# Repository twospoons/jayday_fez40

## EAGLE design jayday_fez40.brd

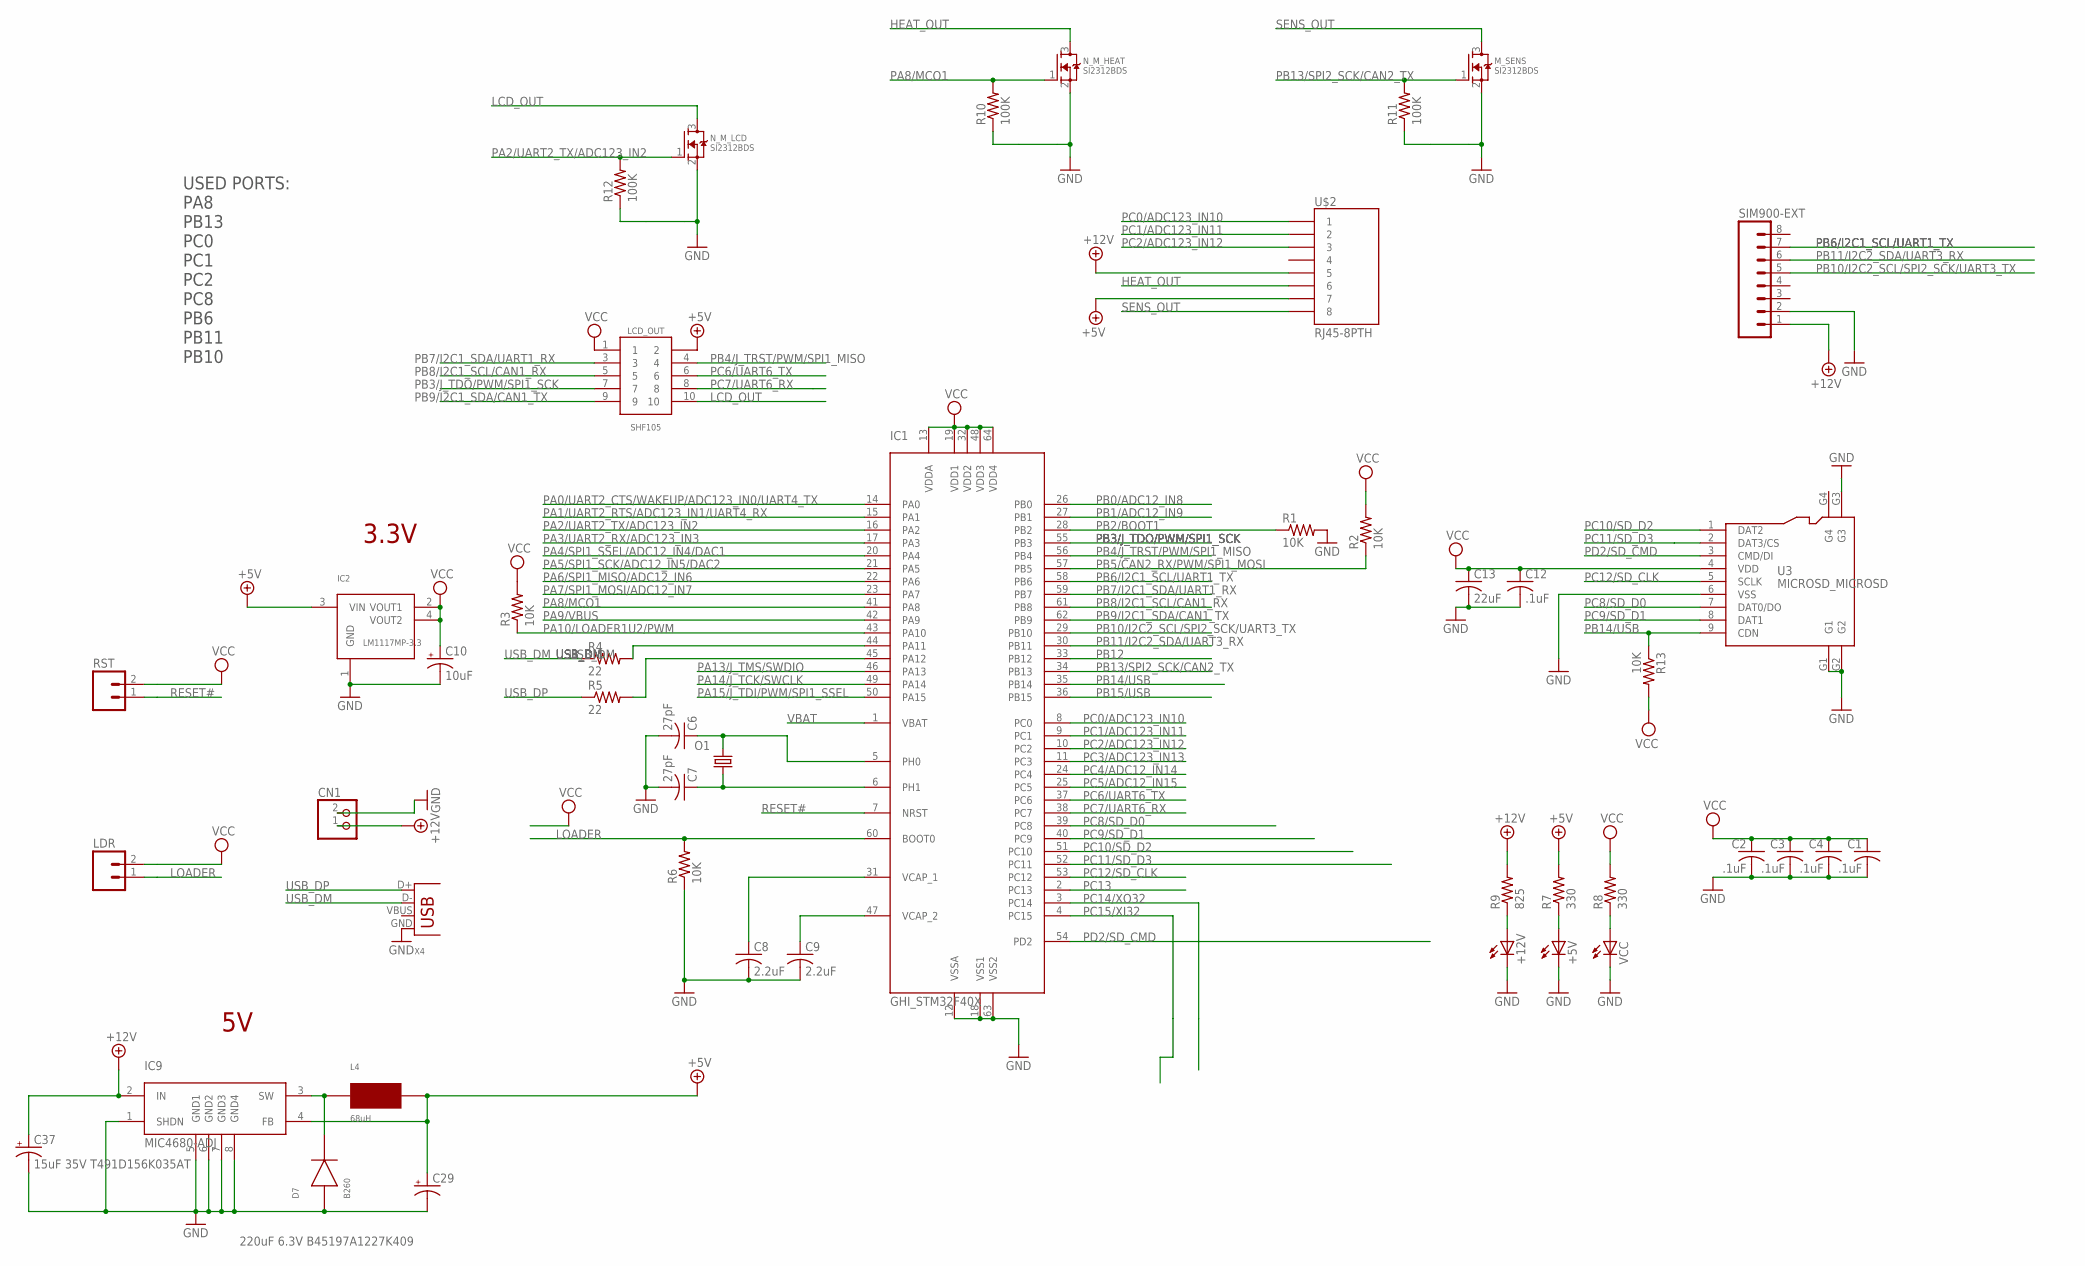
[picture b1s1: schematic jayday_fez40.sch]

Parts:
+5V, +12V: LEDCHIPLED_0805; CHIPLED_0805
C1, C2, C3, C4, C12: .1uF; C0603K
C6, C7: 27pF; C0603K
C8, C9: 2.2uF; C0805K
C10: 10uF; CT3528
C13: 22uF; C0805K
C29: 220uF 6.3V B45197A1227K409; D/7343-31W
C37: 15uF 35V T491D156K035AT; D/7343-31W
CN1: JST_2PIN-THM-RA; JST-PH-2-THM-RA
D7: B260; DIODE_SMA
IC1: GHI_STM32F40X; GHI_LQFP64
IC2: LM1117MP-3.3; SOT223
IC9: MIC4680-ADJ; SO8
L4: 68uH; UP2BXXX
LCD_OUT: SHF105; GAD_PAC_SMD
LDR: M02PTH; 1X02
M_SENS: SI2312BDS; TO-236
N_M_HEAT: SI2312BDS; TO-236
N_M_LCD: SI2312BDS; TO-236
O1: 12Mhz; SM49@1
R1, R2, R3, R6, R13: 10K; R0603
R4, R5: 22; R0603
R7, R8: 330; R0603
R9: 825; R0603
R10, R11, R12: 100K; R0603
RST: M02PTH; 1X02
SIM900-EXT: M081X08; 1X08
U3: MICROSD_MICROSD
U$2: RJ45-8PTH; RJ45-8
VCC: LEDCHIPLED_0805; CHIPLED_0805
X4: DX2R005HN2E700; USB-MB-S

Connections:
+5V: C29.+, IC2.3 (VIN), IC9.4 (FB), L4.P$2 (2), LCD_OUT.2, R7.2, U$2.7
+12V: C37.+, CN1.1 (2), IC9.2 (IN), R9.2, SIM900-EXT.1, U$2.5
GND: +5V.C, +12V.C, C1.2, C2.2, C3.2, C4.2, C6.2, C7.2, C8.2, C9.2, C10.-, C12.2, C13.2, C29.-, C37.-, CN1.2 (1), D7.A, IC1.12 (VSSA), IC1.18 (VSS1), IC1.63 (VSS2), IC2.1 (GND), IC9.1 (SHDN), IC9.5 (GND1), IC9.6 (GND2), IC9.7 (GND3), IC9.8 (GND4), M_SENS.2 (S), N_M_HEAT.2 (S), N_M_LCD.2 (S), R1.2, R6.1, R10.1, R11.1, R12.1, SIM900-EXT.2, U3.6 (VSS), U3.G1, U3.G2, U3.G3, VCC.C, X4.GND
HEAT_OUT: N_M_HEAT.3 (D), U$2.6
LCD_OUT: LCD_OUT.10, N_M_LCD.3 (D)
LOADER: IC1.60 (BOOT0), LDR.1, R6.2
unnamed: C9.1, IC1.47 (VCAP_2)
unnamed: C8.1, IC1.31 (VCAP_1)
unnamed: IC1.44 (PA11), R4.2
unnamed: IC1.45 (PA12), R5.2
unnamed: D7.K, IC9.3 (SW), L4.P$1 (1)
unnamed: +5V.A, R7.1
unnamed: R8.1, VCC.A
unnamed: +12V.A, R9.1
PA0/UART2_CTS/WAKEUP/ADC123_IN0/UART4_TX: IC1.14 (PA0)
PA1/UART2_RTS/ADC123_IN1/UART4_RX: IC1.15 (PA1)
PA2/UART2_TX/ADC123_IN2: IC1.16 (PA2), N_M_LCD.1 (G), R12.2
PA3/UART2_RX/ADC123_IN3: IC1.17 (PA3)
PA4/SPI1_SSEL/ADC12_IN4/DAC1: IC1.20 (PA4)
PA5/SPI1_SCK/ADC12_IN5/DAC2: IC1.21 (PA5)
PA6/SPI1_MISO/ADC12_IN6: IC1.22 (PA6)
PA7/SPI1_MOSI/ADC12_IN7: IC1.23 (PA7)
PA8/MCO1: IC1.41 (PA8), N_M_HEAT.1 (G), R10.2
PA9/VBUS: IC1.42 (PA9)
PA10/LOADER1U2/PWM: IC1.43 (PA10), R3.1
PA13/J_TMS/SWDIO: IC1.46 (PA13)
PA14/J_TCK/SWCLK: IC1.49 (PA14)
PA15/J_TDI/PWM/SPI1_SSEL: IC1.50 (PA15)
PB0/ADC12_IN8: IC1.26 (PB0)
PB1/ADC12_IN9: IC1.27 (PB1)
PB2/BOOT1: IC1.28 (PB2), R1.1
PB3/J_TDO/PWM/SPI1_SCK: IC1.55 (PB3), LCD_OUT.7
PB4/J_TRST/PWM/SPI1_MISO: IC1.56 (PB4), LCD_OUT.4
PB5/CAN2_RX/PWM/SPI1_MOSI: IC1.57 (PB5), R2.1
PB6/I2C1_SCL/UART1_TX: IC1.58 (PB6), SIM900-EXT.7
PB7/I2C1_SDA/UART1_RX: IC1.59 (PB7), LCD_OUT.3
PB8/I2C1_SCL/CAN1_RX: IC1.61 (PB8), LCD_OUT.5
PB9/I2C1_SDA/CAN1_TX: IC1.62 (PB9), LCD_OUT.9
PB10/I2C2_SCL/SPI2_SCK/UART3_TX: IC1.29 (PB10), SIM900-EXT.5
PB11/I2C2_SDA/UART3_RX: IC1.30 (PB11), SIM900-EXT.6
PB12: IC1.33 (PB12)
PB13/SPI2_SCK/CAN2_TX: IC1.34 (PB13), M_SENS.1 (G), R11.2
PB14/USB: IC1.35 (PB14), R13.1, U3.9 (CDN)
PB15/USB: IC1.36 (PB15)
PC0/ADC123_IN10: IC1.8 (PC0), U$2.1
PC1/ADC123_IN11: IC1.9 (PC1), U$2.2
PC2/ADC123_IN12: IC1.10 (PC2), U$2.3
PC3/ADC123_IN13: IC1.11 (PC3)
PC4/ADC12_IN14: IC1.24 (PC4)
PC5/ADC12_IN15: IC1.25 (PC5)
PC6/UART6_TX: IC1.37 (PC6), LCD_OUT.6
PC7/UART6_RX: IC1.38 (PC7), LCD_OUT.8
PC8/SD_D0: IC1.39 (PC8), U3.7 (DAT0/DO)
PC9/SD_D1: IC1.40 (PC9), U3.8 (DAT1)
PC10/SD_D2: IC1.51 (PC10), U3.1 (DAT2)
PC11/SD_D3: IC1.52 (PC11), U3.2 (DAT3/CS)
PC12/SD_CLK: IC1.53 (PC12), U3.5 (SCLK)
PC13: IC1.2 (PC13)
PC14/XO32: IC1.3 (PC14)
PC15/XI32: IC1.4 (PC15)
PD2/SD_CMD: IC1.54 (PD2), U3.3 (CMD/DI)
RESET#: IC1.7 (NRST), RST.1
SENS_OUT: M_SENS.3 (D), U$2.8
USB_DM: R4.1, X4.D-
USB_DP: R5.1, X4.D+
VBAT: IC1.1 (VBAT)
VCC: C1.1, C2.1, C3.1, C4.1, C10.+, C12.1, C13.1, IC1.13 (VDDA), IC1.19 (VDD1), IC1.32 (VDD2), IC1.48 (VDD3), IC1.64 (VDD4), IC2.2 (VOUT1), IC2.4 (VOUT2), LCD_OUT.1, LDR.2, R2.2, R3.2, R8.2, R13.2, RST.2, U3.4 (VDD)
XTAL3: C6.1, IC1.5 (PH0), O1.2
XTAL4: C7.1, IC1.6 (PH1), O1.1

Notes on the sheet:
3.3V
USED PORTS: PA8 PB13 PC0 PC1 PC2 PC8 PB6 PB11 PB10

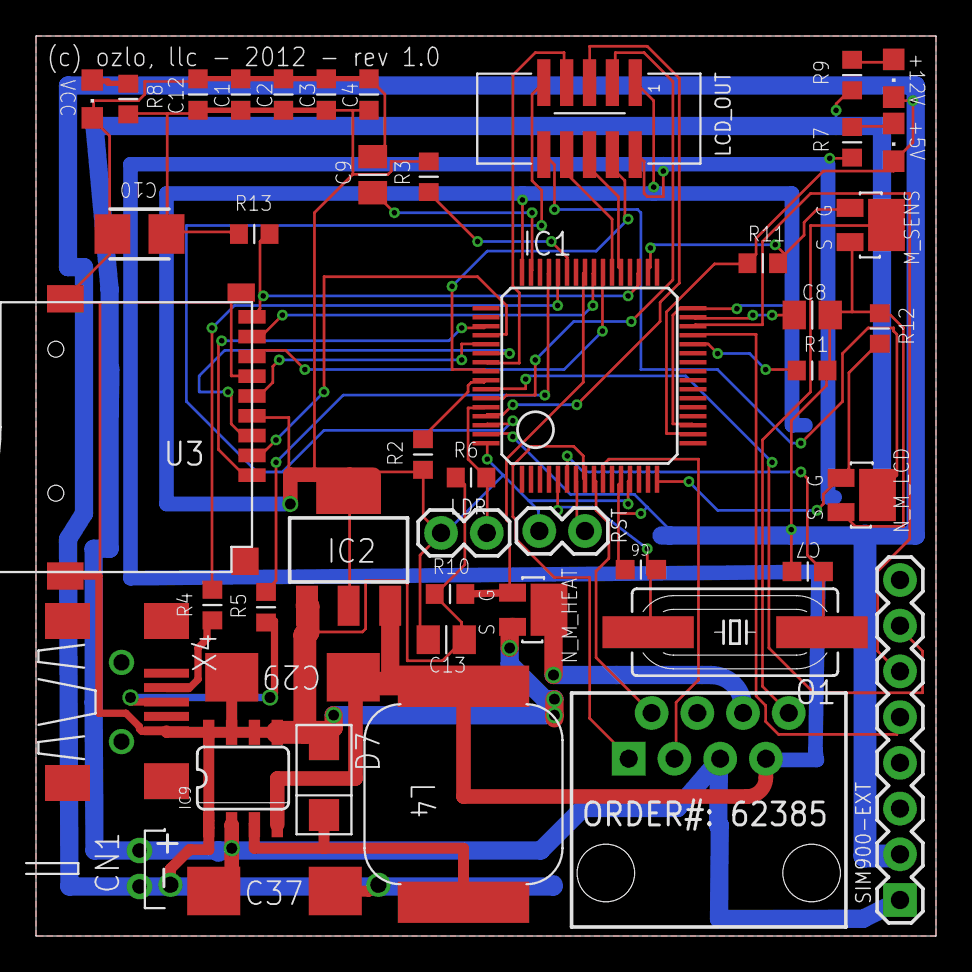
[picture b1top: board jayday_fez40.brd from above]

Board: 2 copper layers, 50.0 x 50.0 mm, 46 parts (0 on the bottom side), 47 nets.

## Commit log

2012-10-23 custom stmf impl
2012-10-24 layed out board.. 2 traces left
2012-10-25 finished layout
2012-10-26 added bom, and shipped pcb
2012-10-26 fixed R9 to 825ohms
2012-11-04 Added bom

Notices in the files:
parts and their libraries:
SparkFun-Connectors: Licensing: CC v3.0 Share-Alike You are welcome to use this library for commercial purposes.
